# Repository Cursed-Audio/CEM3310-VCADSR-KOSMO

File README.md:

# CEM3310-VCADSR-KOSMO
a CEM3310 based Voltage controlled ADSR with a trigger button. main PCB panel and jack board v2.2

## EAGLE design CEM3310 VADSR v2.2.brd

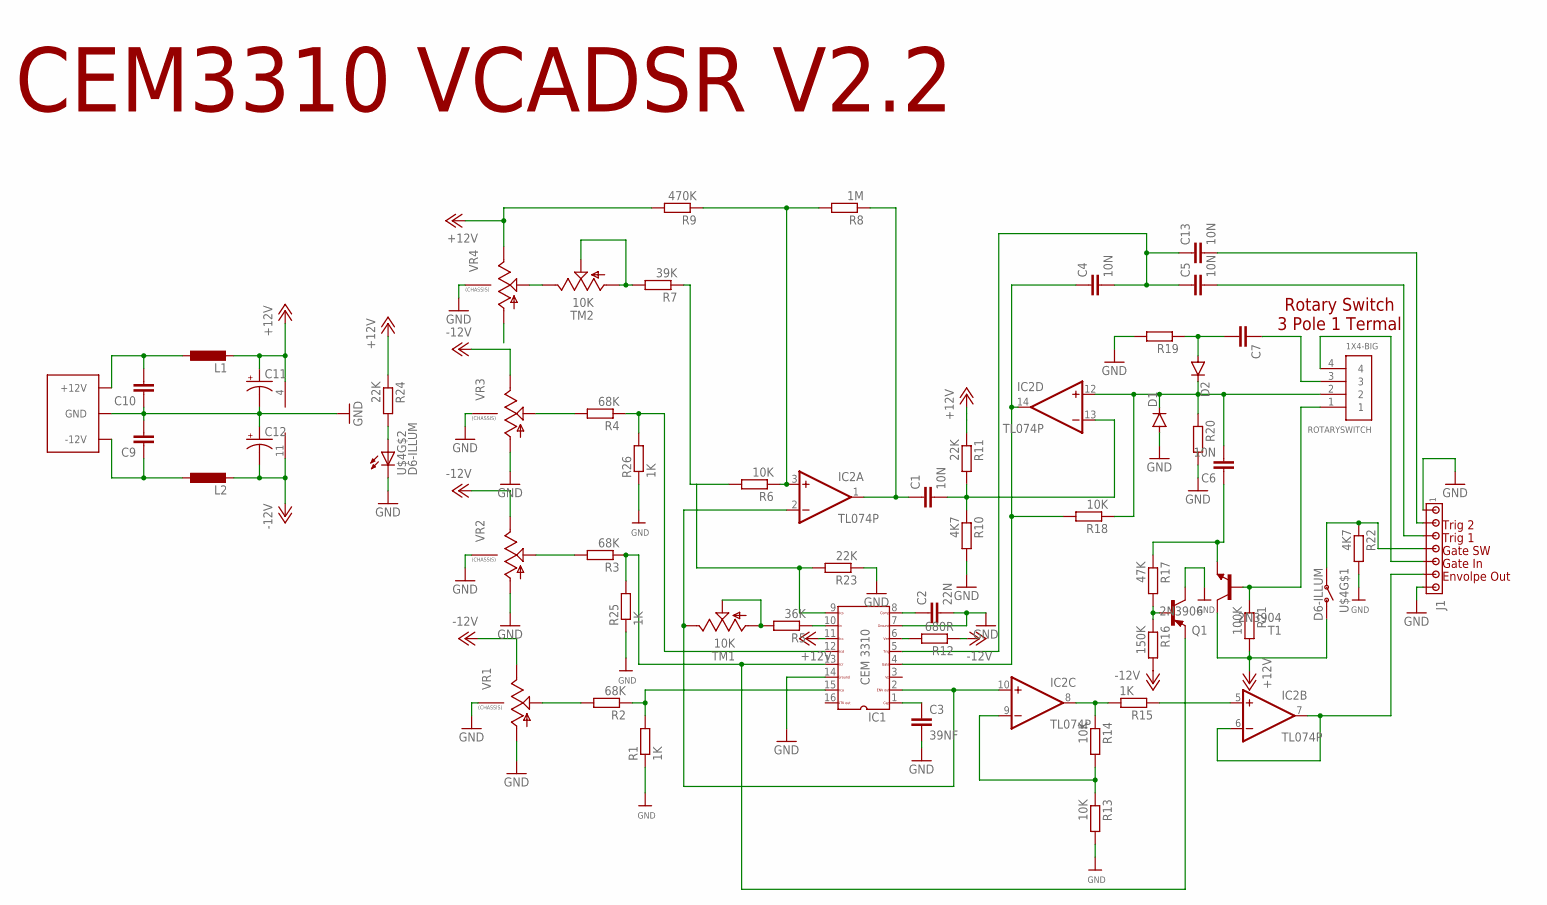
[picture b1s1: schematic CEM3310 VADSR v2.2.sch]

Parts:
C1, C4, C5, C6, C13: 10N; C050-025X075
C2: 22N; C050-025X075
C3: 39NF; C050-025X075
C7, C9, C10: C-EU050-025X075; C050-025X075
C8: EURO_POWER_LOCKSKINNY; EURO_POWER_HEADER
C11, C12: CAPACITOR-PE2.5-6; E2,5-6
D1: OA95; DO35-7
D2: 1N4148DO35-7; DO35-7
IC1: CEM3310; DIL16
IC2: TL074P; DIL14
J1: MTA07-100; 10X07MTA
L1, L2: L-EU0207/7; 0207/7
Q1: 2N3906; TO92
R1, R15, R25, R26: 1K; 0207/7
R2, R3, R4: 68K; 0207/7
R5: 36K; 0207/7
R6, R13, R14, R18: 10K; 0207/7
R7: 39K; 0207/7
R8: 1M; 0207/7
R9: 470K; 0207/7
R10, R22: 4K7; 0207/7
R11, R23, R24: 22K; 0207/7
R12: 680R; 0207/7
R16: 150K; 0207/7
R17: 47K; 0207/7
R19, R20: R-EU_0207/7; 0207/7
R21: 100K; 0207/7
ROTARYSWITCH: 1X4-BIG; 1X04-BIG
T1: 2N3904; TO92
TM1, TM2: 10K; 6MM
U$4: D6-ILLUM; D6_PUSH_SWITCH_ILLUM
VR1, VR2, VR3, VR4: 9MM_SNAP-IN_POT_CHASSIS; 9MM_SNAP-IN_POT

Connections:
+12V: C11.+, IC1.11, IC2.4 (V+), L1.2, R9.2, R11.1, R21.2, R24.1, T1.1 (C), U$4.P$1 (O), U$4.P$2 (O), VR4.3 (E)
-12V: C12.-, IC2.11 (V-), L2.2, R12.1, R16.2, VR1.3 (E), VR2.3 (E), VR3.3 (E)
GND: C2.2, C3.2, C8.3 (GND), C8.4 (GND), C8.5 (GND), C8.6 (GND), C8.7 (GND), C8.8 (GND), C9.2, C10.1, C11.-, C12.+, D1.A, IC1.7, IC1.14, J1.1, J1.7, Q1.1 (C), R1.1, R10.2, R13.2, R19.2, R20.2, R22.2, R23.1, R25.1, R26.1, U$4.LED- (C), VR1.1 (A), VR1.CHASSIS1, VR1.CHASSIS2, VR2.1 (A), VR2.CHASSIS1, VR2.CHASSIS2, VR3.1 (A), VR3.CHASSIS1, VR3.CHASSIS2, VR4.CHASSIS1, VR4.CHASSIS2
GND1: VR4.1 (A)
unnamed: C3.1, IC1.1
unnamed: IC1.15, R1.2, R2.1
unnamed: R2.2, VR1.2 (S)
unnamed: IC2.5 (+IN), R15.1
unnamed: IC1.13, Q1.3 (E), R3.1, R25.2
unnamed: R3.2, VR2.2 (S)
unnamed: IC2.6 (-IN), IC2.7 (OUT), J1.6
unnamed: IC1.12, R4.1, R26.2
unnamed: R4.2, VR3.2 (S)
unnamed: C7.1, ROTARYSWITCH.3
unnamed: R5.2, TM1.A, TM1.S
unnamed: IC1.10, R5.1
unnamed: IC1.2, IC2.2 (-IN), IC2.10 (+IN), TM1.E
unnamed: IC1.9, R6.2, R7.1, R23.2
unnamed: C1.1, IC2.1 (OUT), R8.1
unnamed: R7.2, TM2.A, TM2.S
unnamed: IC2.3 (+IN), R6.1, R8.2, R9.1
unnamed: TM2.E, VR4.2 (S)
unnamed: C1.2, IC2.13 (-IN), R10.1, R11.2
unnamed: J1.5, ROTARYSWITCH.4
unnamed: C13.2, J1.2
unnamed: IC1.6, R12.2
unnamed: C5.2, J1.3
unnamed: C2.1, IC1.8
unnamed: IC2.9 (-IN), R13.1, R14.2
unnamed: IC2.8 (OUT), R14.1, R15.2
unnamed: C6.1, R17.1, T1.3 (E)
unnamed: Q1.2 (B), R16.1, R17.2
unnamed: C6.2, D1.C, D2.C, IC2.12 (+IN), R18.1, R20.1, ROTARYSWITCH.2
unnamed: C4.1, IC1.4, IC2.14 (OUT), R18.2
unnamed: C4.2, C5.1, C13.1, IC1.5
unnamed: C7.2, D2.A, R19.1
unnamed: R21.1, ROTARYSWITCH.1, T1.2 (B)
unnamed: J1.4, R22.1, U$4.P$3, U$4.P$4
unnamed: R24.2, U$4.LED+ (A)
unnamed: C8.9 (+12V), C8.10 (+12V), C10.2, L1.1
unnamed: C8.1 (-12V), C8.2 (-12V), C9.1, L2.1

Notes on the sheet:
Envolpe Out
Gate In
Gate SW
Trig 1
Trig 2
CEM3310 VCADSR V2.2
Rotary Switch 3 Pole 1 Termal

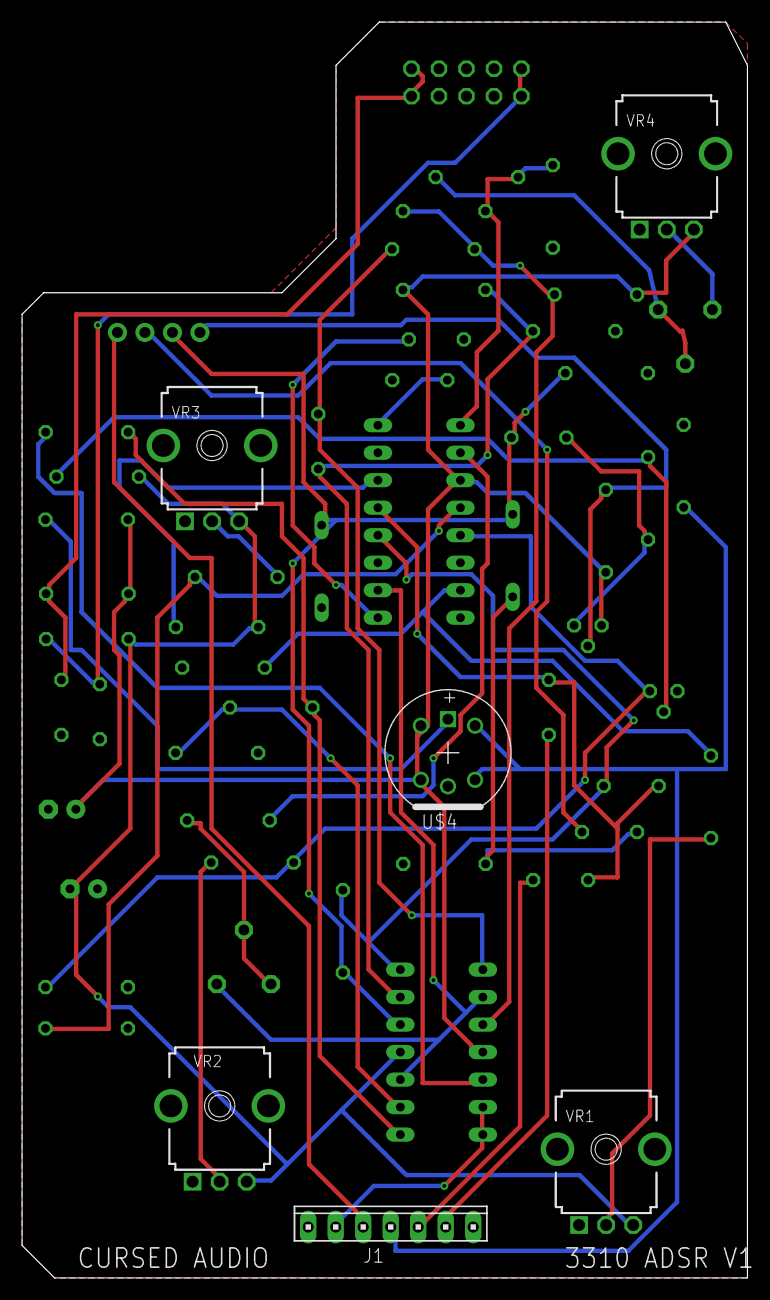
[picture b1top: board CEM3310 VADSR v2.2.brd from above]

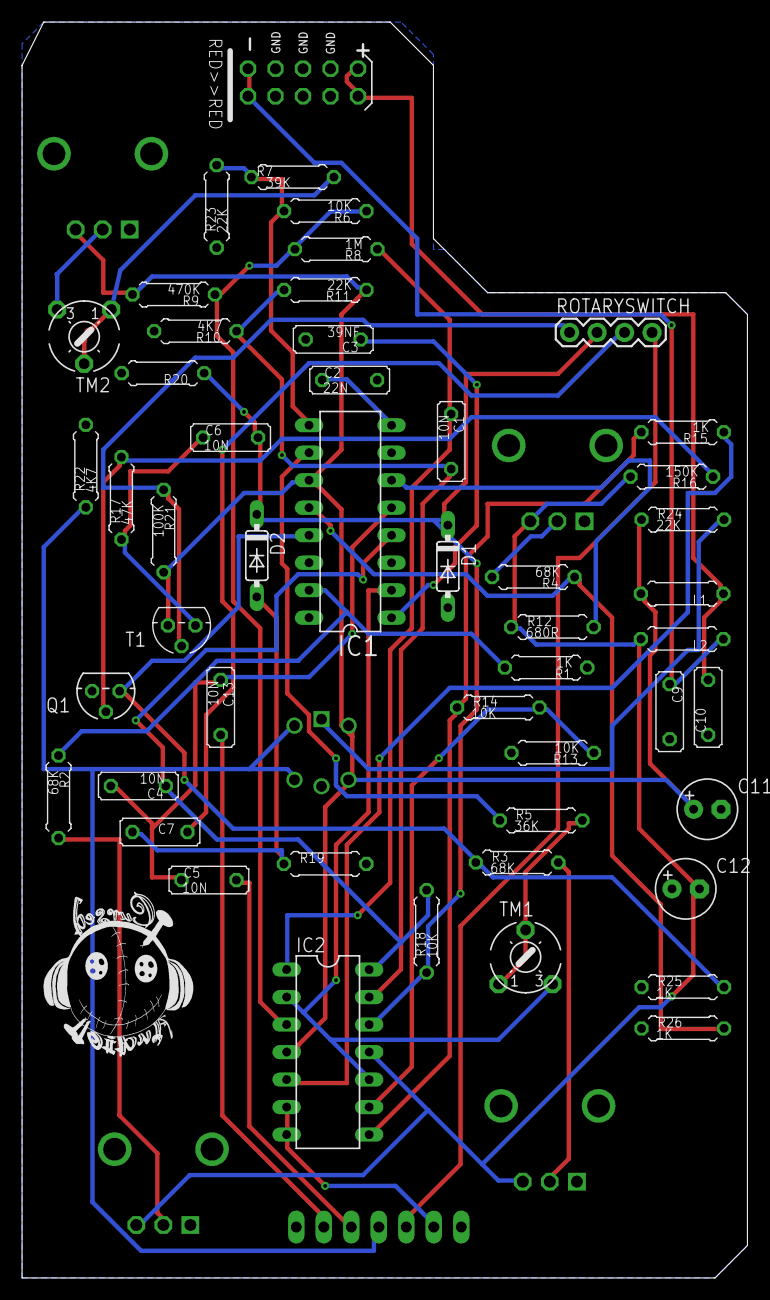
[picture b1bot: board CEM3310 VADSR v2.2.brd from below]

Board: 2 copper layers, 67.0 x 116.0 mm, 57 parts (50 on the bottom side), 40 nets.

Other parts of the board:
U$8: CA

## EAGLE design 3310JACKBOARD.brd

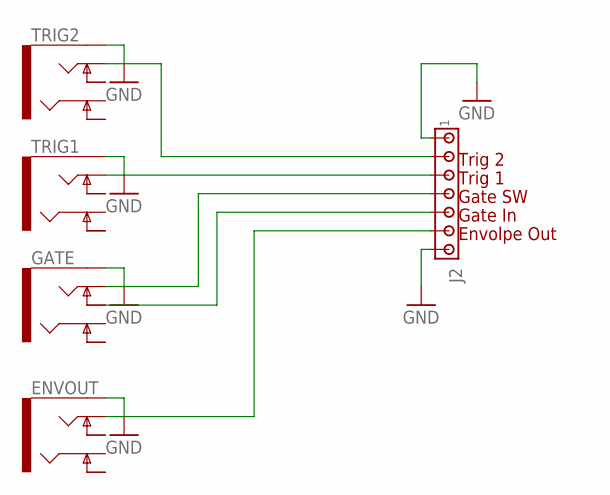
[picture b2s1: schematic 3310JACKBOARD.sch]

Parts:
ENVOUT: AUDIO_JACK_TRS_0.25"_PTH_VERTICAL; AUDIO_JACK_0.25"_TRS_PTH_VERTICAL
GATE: AUDIO_JACK_TRS_0.25"_PTH_VERTICAL; AUDIO_JACK_0.25"_TRS_PTH_VERTICAL
J2: MTA07-100; 10X07MTA
TRIG1, TRIG2: AUDIO_JACK_TRS_0.25"_PTH_VERTICAL; AUDIO_JACK_0.25"_TRS_PTH_VERTICAL

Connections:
GND: ENVOUT.SLEEVE (EARTH), GATE.SLEEVE (EARTH), J2.1, J2.7, TRIG1.SLEEVE (EARTH), TRIG2.SLEEVE (EARTH)
unnamed: ENVOUT.TIP, J2.6
unnamed: GATE.TIP-NORM, J2.5
unnamed: GATE.TIP, J2.4
unnamed: J2.3, TRIG1.TIP
unnamed: J2.2, TRIG2.TIP

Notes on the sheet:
Envolpe Out
Gate In
Gate SW
Trig 1
Trig 2

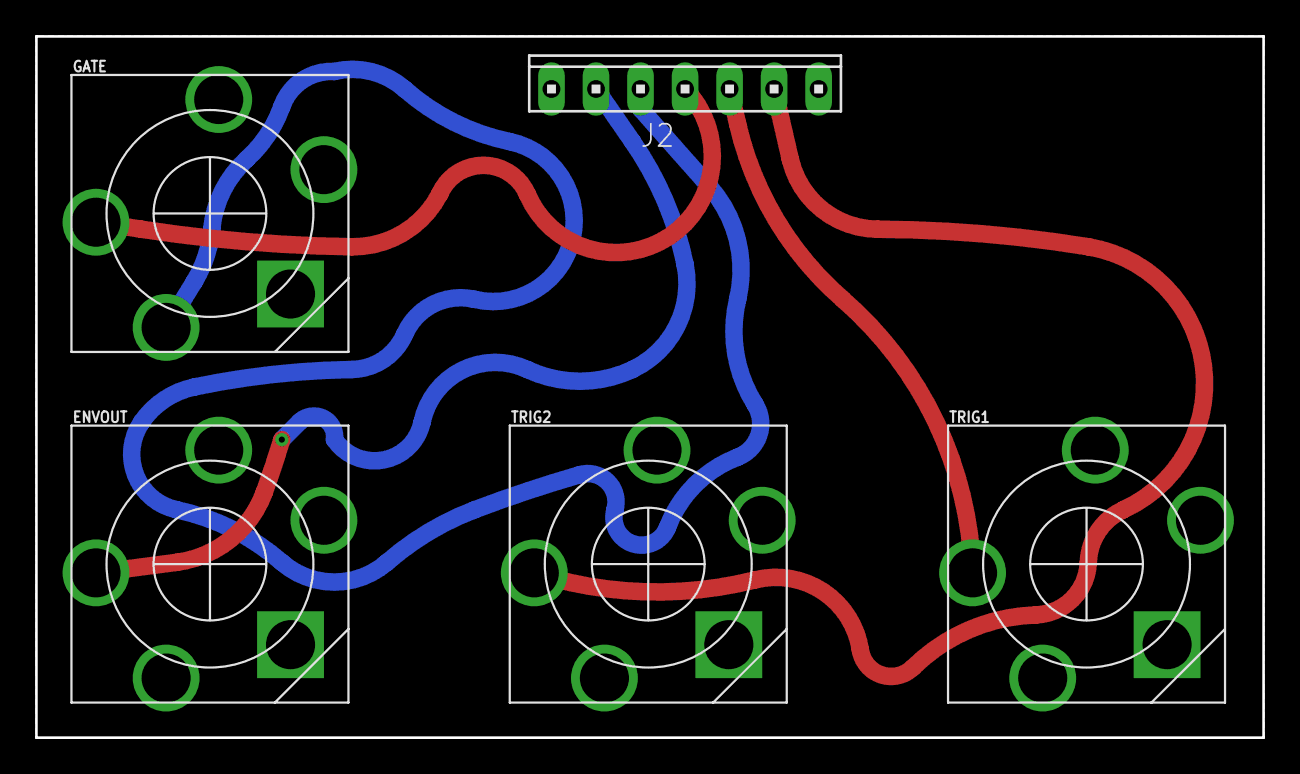
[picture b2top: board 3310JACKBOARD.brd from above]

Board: 2 copper layers, 70.0 x 40.0 mm, 6 parts (0 on the bottom side), 6 nets.

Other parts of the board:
U$1: CA

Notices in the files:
parts and their libraries:
SparkFun-Retired: Licensing: Creative Commons ShareAlike 4.0 International - https://creativecommons.org/licenses/by-sa/4.0
